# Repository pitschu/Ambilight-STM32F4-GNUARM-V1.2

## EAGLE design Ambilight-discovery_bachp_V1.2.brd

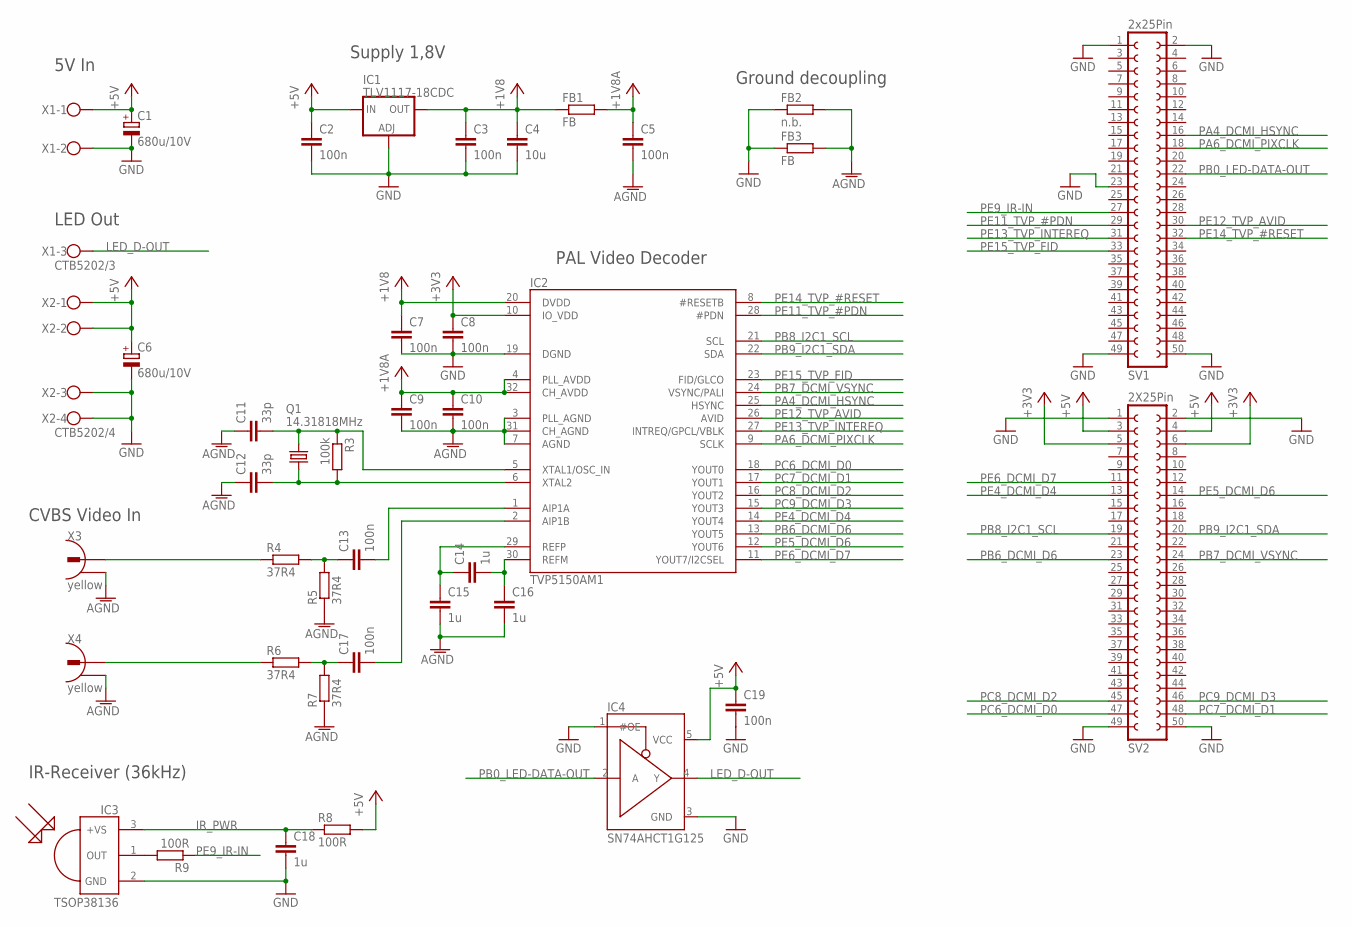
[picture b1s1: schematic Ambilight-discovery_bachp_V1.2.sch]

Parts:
C1, C6: 680u/10V; 153CLV-1012
C2, C3, C5, C7, C8, C9, C10, C13, C17, C19: 100n; C0805
C4: 10u; C1210
C11, C12: 33p; C0805
C14, C15, C16, C18: 1u; C0805
FB1, FB3: FB; R0805
FB2: n.b.; R0805
IC1: TLV1117-18CDC; SOT223
IC2: TVP5150AM1; TQFP32-0.5MM
IC3: TSOP38136; TSOP38XXX
IC4: SN74AHCT1G125; SOT23-5L
Q1: 14.31818MHz; HC49UP
R3: 100k; R0805
R4, R5, R6, R7: 37R4; R0805
R8, R9: 100R; R0805
SV1: 2x25Pin; FE25-2
SV2: 2X25Pin; FE25-2
X1: CTB5202/3; W237-103
X2: CTB5202/4; W237-4
X3, X4: yellow; CINCH_JALCO

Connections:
+1V8: C3.1, C4.1, C7.1, FB1.1, IC1.2 (OUT), IC1.4 (OUT), IC2.20 (DVDD)
+1V8A: C5.1, C9.1, C10.1, FB1.2, IC2.4 (PLL_AVDD), IC2.32 (CH_AVDD)
+3V3: C8.1, IC2.10 (IO_VDD), SV2.5, SV2.6
+5V: C1.+, C2.1, C6.+, C19.1, IC1.3 (IN), IC4.5 (VCC), R8.2, SV2.3, SV2.4, X1.1, X2.1, X2.2
AGND: C5.2, C9.2, C10.2, C11.1, C12.1, C15.2, C16.2, FB2.2, FB3.2, IC2.3 (PLL_AGND), IC2.7 (AGND), IC2.31 (CH_AGND), R5.1, R7.1, X3.2, X4.2
GND: C1.-, C2.2, C3.2, C4.2, C6.-, C7.2, C8.2, C18.2, C19.2, FB2.1, FB3.1, IC1.1 (ADJ), IC2.19 (DGND), IC3.2 (GND), IC4.1 (#OE), IC4.3 (GND), SV1.1, SV1.2, SV1.23, SV1.49, SV1.50, SV2.1, SV2.2, SV2.49, SV2.50, X1.2, X2.3, X2.4
IR_PWR: C18.1, IC3.3 (+VS), R8.1
LED_D-OUT: IC4.4 (Y), X1.3
unnamed: C14.1, C15.1, IC2.29 (REFP)
unnamed: C14.2, C16.1, IC2.30 (REFM)
unnamed: C17.1, R6.2, R7.2
unnamed: C17.2, IC2.2 (AIP1B)
unnamed: C13.2, IC2.1 (AIP1A)
unnamed: C13.1, R4.2, R5.2
unnamed: R4.1, X3.1
unnamed: C11.2, IC2.5 (XTAL1/OSC_IN), Q1.1, R3.1
unnamed: C12.2, IC2.6 (XTAL2), Q1.2, R3.2
unnamed: R6.1, X4.1
unnamed: IC3.1 (OUT), R9.2
PA4_DCMI_HSYNC: IC2.25 (HSYNC), SV1.16
PA6_DCMI_PIXCLK: IC2.9 (SCLK), SV1.18
PB0_LED-DATA-OUT: IC4.2 (A), SV1.22
PB6_DCMI_D6: IC2.13 (YOUT5), SV2.23
PB7_DCMI_VSYNC: IC2.24 (VSYNC/PALI), SV2.24
PB8_I2C1_SCL: IC2.21 (SCL), SV2.19
PB9_I2C1_SDA: IC2.22 (SDA), SV2.20
PC6_DCMI_D0: IC2.18 (YOUT0), SV2.47
PC7_DCMI_D1: IC2.17 (YOUT1), SV2.48
PC8_DCMI_D2: IC2.16 (YOUT2), SV2.45
PC9_DCMI_D3: IC2.15 (YOUT3), SV2.46
PE4_DCMI_D4: IC2.14 (YOUT4), SV2.13
PE5_DCMI_D6: IC2.12 (YOUT6), SV2.14
PE6_DCMI_D7: IC2.11 (YOUT7/I2CSEL), SV2.11
PE9_IR-IN: R9.1, SV1.27
PE11_TVP_#PDN: IC2.28 (#PDN), SV1.29
PE12_TVP_AVID: IC2.26 (AVID), SV1.30
PE13_TVP_INTEREQ: IC2.27 (INTREQ/GPCL/VBLK), SV1.31
PE14_TVP_#RESET: IC2.8 (#RESETB), SV1.32
PE15_TVP_FID: IC2.23 (FID/GLCO), SV1.33

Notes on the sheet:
5V In
LED Out
Supply 1,8V
Ground decoupling
CVBS Video In
PAL Video Decoder
IR-Receiver (36kHz)

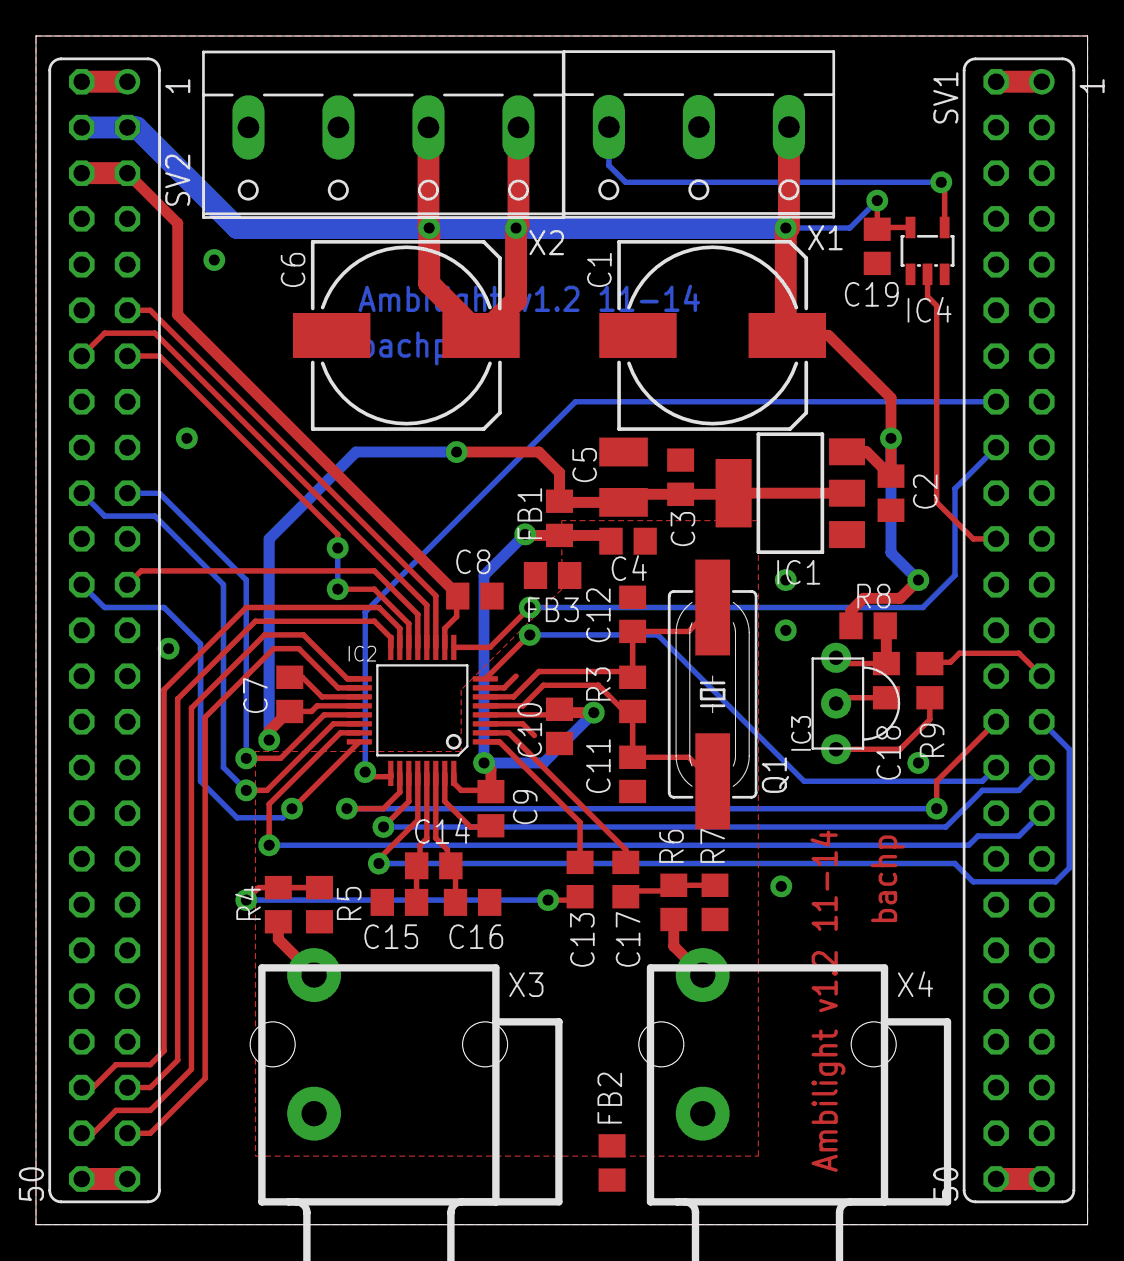
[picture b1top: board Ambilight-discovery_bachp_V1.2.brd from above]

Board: 2 copper layers, 58.4 x 66.0 mm, 40 parts (0 on the bottom side), 39 nets.

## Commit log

2014-05-02 Published version (mikrocontroller.net) without physical LED number setting (fixed 48*28 LEDs)
2014-05-04 Added code for: - Support of blue button (Mode selct: Ambi/Mood/Standby) - Set physical LED count: 'P' = width; 'R' = height; MAX = 80x60 - Fixed bugs in flashparams.c - Added 'N' = Reset TVP5150 and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
2014-05-05 Added AGC on/off switch Some minor bug fixes and comments
2014-05-10 Got warning (__packed already defed) in USB header with GCC 4.8.3.
2014-07-25 V1.2 - fixed bugs in tvp5150:dcmi.c (SLOTs devider) - added dynFramesLimit - some default values updated - avoid black-flickering (ambiLight.c)
2014-07-25 minor changes
2015-03-06 Updated GNU-ARM eclipse tools and toolchain 4.9.3
2015-03-06 Revert "Updated GNU-ARM eclipse tools and toolchain 4.9.3"
    This reverts commit 6c42dfe02f2de7abf1f6423b96cd0f630189174d.
2015-03-06 commited LD-scripts
2016-05-22 Revert "commited LD-scripts"
    This reverts commit 36b9519e987111be8b39ecca8cf5f9a9a22456c3.
2016-05-22 Updated Eagle files and documents
2017-03-21 Set theme jekyll-theme-cayman
2018-01-11 Update AvrXFifo.c
    Added deugging
